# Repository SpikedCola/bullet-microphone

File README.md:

# bullet-microphone

A microphone to use outdoors for a BirdNET station, built around the [PUI Audio AOM-5024 electret capsule](./AOM-5024L-HD-F-R.pdf). 

The housing is a 3D-printed bullet with the capsule pressed into the nose, and a small preamp board inside the body.

The capsule is designed to be easily replaceable if it fails due to weather exposure.
The threaded connection and cable strain relief are waterproofed by covering with glue-filled heatshrink tubing.

It seems to work well. It has been exposed for a year to the elements and still sounds just fine. It is a lot more sensitive than I expected.

## Pre-Amp Circuit

The preamp is a discrete circuit powered by phantom power, based on [ESP Project 93](https://sound-au.com/project93.htm):

| Pin (J2) | XLR |
|---|---|
| 1 | Ground |
| 2 | Hot (signal + phantom) |
| 3 | Cold (phantom, AC-grounded) |

## PCB

The PCB is designed to be inserted into a T-shaped slot in the housing. When selecting the capacitors,
height was a consideration.

## Case

## Notes For Next Revision
- Space the electrolytic caps out a little more. They currently *just* touch, and lean slightly. Or select different capacitors.
- Label the I/O pins on both sides if there is room.

## Build

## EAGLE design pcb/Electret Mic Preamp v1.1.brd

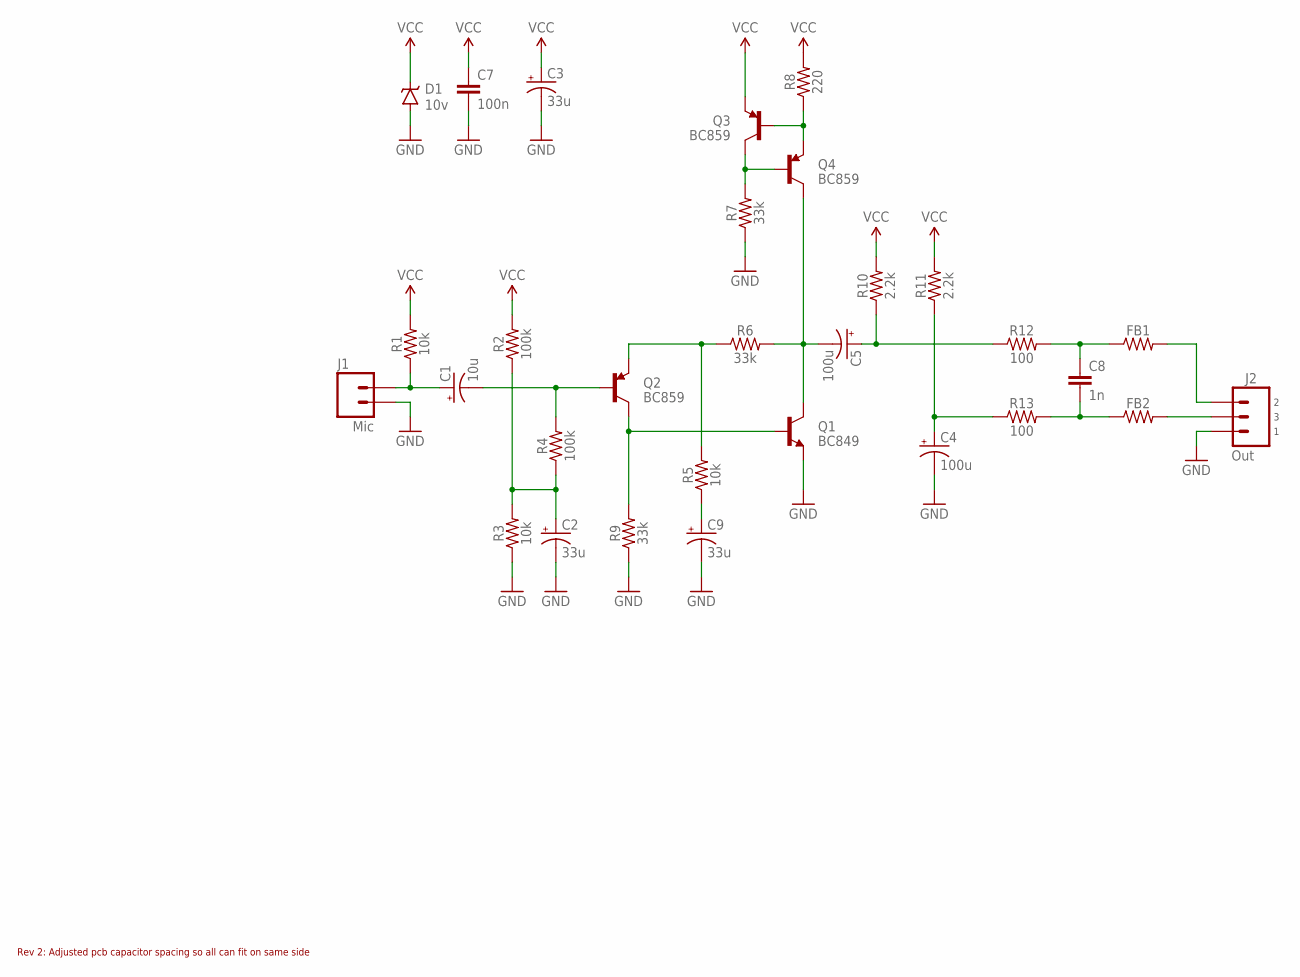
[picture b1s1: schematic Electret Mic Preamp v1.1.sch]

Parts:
C1: 10u; E1,8-4
C2, C3, C9: 33u; E2,5-6
C4, C5: 100u; E2,5-6
C7: 100n; C0603
C8: 1n; C0603
D1: 10v; SOD-123
FB1, FB2: RESISTORR0603; R0603
J1: Mic; 1X02
J2: Out; 1X03
Q1: BC849; SOT23-3
Q2, Q3, Q4: BC859; SOT23-3
R1, R3, R5: 10k; R0603
R2, R4: 100k; R0603
R6, R7, R9: 33k; R0603
R8: 220; R0603
R10, R11: 2.2k; R0603
R12, R13: 100; R0603

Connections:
GND: C2.-, C3.-, C4.-, C7.2, C9.-, D1.A, J1.2, J2.3, Q1.2 (E), R3.1, R7.1, R9.1
unnamed: C1.+, J1.1, R1.1
unnamed: Q3.3 (C), Q4.1 (B), R7.2
unnamed: C2.+, R2.1, R3.2, R4.1
unnamed: C1.-, Q2.1 (B), R4.2
unnamed: Q2.2 (E), R5.2, R6.1
unnamed: Q1.1 (B), Q2.3 (C), R9.2
unnamed: C9.+, R5.1
unnamed: Q3.1 (B), Q4.2 (E), R8.1
unnamed: C5.-, Q1.3 (C), Q4.3 (C), R6.2
unnamed: C5.+, R10.1, R12.1
unnamed: C4.+, R11.1, R13.1
unnamed: C8.1, FB1.1, R12.2
unnamed: C8.2, FB2.1, R13.2
unnamed: FB2.2, J2.2
unnamed: FB1.2, J2.1
VCC: C3.+, C7.1, D1.C, Q3.2 (E), R1.2, R2.2, R8.2, R10.2, R11.2

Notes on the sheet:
Rev 2: Adjusted pcb capacitor spacing so all can fit on same side

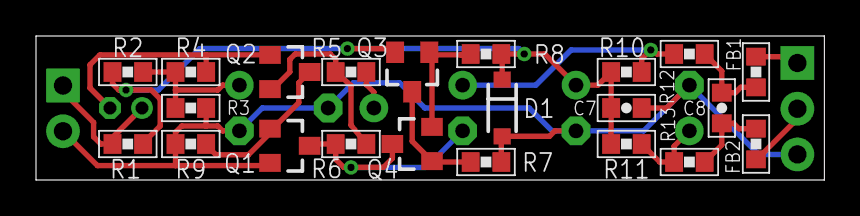
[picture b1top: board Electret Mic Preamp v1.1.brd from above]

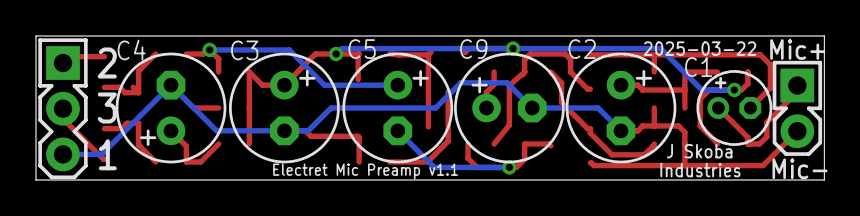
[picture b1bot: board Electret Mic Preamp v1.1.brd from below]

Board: 2 copper layers, 43.8 x 8.0 mm, 30 parts (8 on the bottom side), 17 nets.

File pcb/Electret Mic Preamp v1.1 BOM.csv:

"Qty","Value","Part Num","Package","Parts"
"2","","*","R0603","FB1, FB2"
"1","1n","*","C0603","C8"
"2","2.2k","*","R0603","R10, R11"
"3","10k","*","R0603","R1, R3, R5"
"1","10u","*","E1,8-4","C1"
"1","16V","*","SOD-123","D1"
"3","33k","*","R0603","R6, R7, R9"
"3","33u","*","E2,5-6","C2, C3, C9"
"2","100","*","R0603","R12, R13"
"2","100k","*","R0603","R2, R4"
"1","100n","*","C0603","C7"
"2","100u","*","E2,5-6","C4, C5"
"1","220","*","R0603","R8"
"1","BC849","*","SOT23-3","Q1"
"3","BC859","*","SOT23-3","Q2, Q3, Q4"
"1","Mic","*","1X02","J1"
"1","Out","*","1X03","J2"
